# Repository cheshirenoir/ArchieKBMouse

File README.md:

# ArchieKBMouse
An adapter to allow Archimedes computers to use cheap PS/2 keyboards and mice. This is just a PCB/Schematic based on the hard work of the StarDot forum.
Based on a design by IanB, with some additional decoding by IanS

All I have done is put IanB's work into KiCAD, and designed a PCB off it, using some hinting from the schematic by IanS, so all credit and rights belong to them.
See: https://stardot.org.uk/forums/viewtopic.php?f=16&t=9334

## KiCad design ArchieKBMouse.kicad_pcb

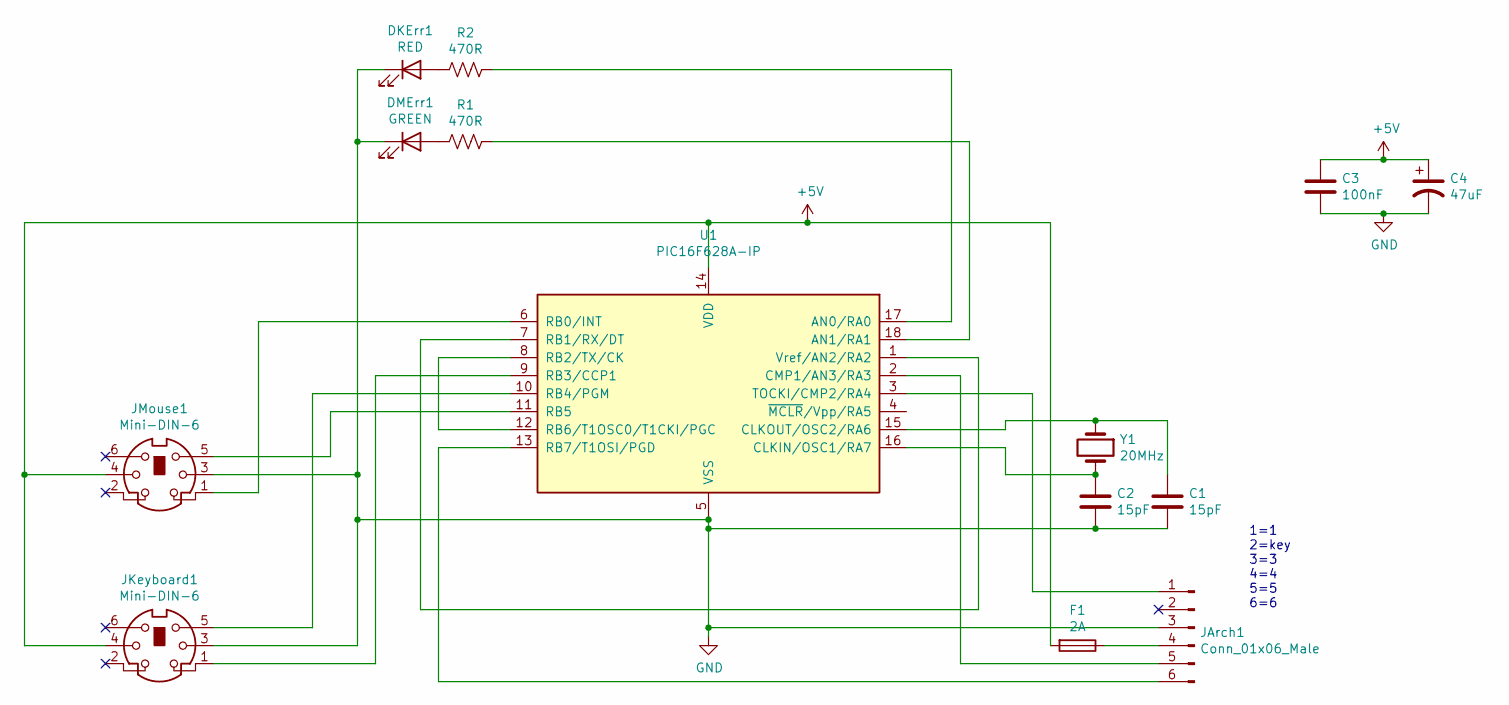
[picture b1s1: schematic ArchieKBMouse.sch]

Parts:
C1, C2: 15pF; C_Disc_D6.0mm_W2.5mm_P5.00mm
C3: 100nF; C_Disc_D6.0mm_W2.5mm_P5.00mm
C4: 47uF; CP_Radial_D5.0mm_P2.50mm
DKErr1: RED; LED_D5.0mm
DMErr1: GREEN; LED_D5.0mm
F1: 2A; Fuseholder_Cylinder-5x20mm_Schurter_FAB_0031-355x_Horizonta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
JArch1: Conn_01x06_Male; PinHeader_1x06_P2.54mm_Horizontal
JKeyboard1: Mini-DIN-6; Mini DIN 6 (PS2)
JMouse1: Mini-DIN-6; Mini DIN 6 (PS2)
R1, R2: 470R; R_Axial_DIN0207_L6.3mm_D2.5mm_P10.16mm_Horizontal
U1: PIC16F628A-IP; DIP-18_W7.62mm_Socket_LongPads
Y1: 20MHz; Crystal_HC49-U_Horizontal_1EP_style2

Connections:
+5V: C3.1, C4.1, F1.2, JKeyboard1.4, JMouse1.4, U1.14 (VDD)
GND: C1.2, C2.2, C3.2, C4.2, DKErr1.1 (K), DMErr1.1 (K), JArch1.3, JKeyboard1.3, JMouse1.3, U1.5 (VSS)
unnamed: C1.1, U1.15 (CLKOUT/OSC2/RA6), Y1.1
unnamed: C2.1, U1.16 (CLKIN/OSC1/RA7), Y1.2
unnamed: DKErr1.2 (A), R2.1
unnamed: DMErr1.2 (A), R1.1
unnamed: F1.1, JArch1.4
unnamed: JArch1.1, U1.3 (TOCKI/CMP2/RA4)
unnamed: JArch1.5, U1.2 (CMP1/AN3/RA3)
unnamed: JArch1.6, U1.13 (RB7/T1OSI/PGD)
unnamed: JKeyboard1.1, U1.9 (RB3/CCP1)
unnamed: JKeyboard1.5, U1.10 (RB4/PGM)
unnamed: JMouse1.1, U1.6 (RB0/INT)
unnamed: JMouse1.5, U1.11 (RB5)
unnamed: R1.2, U1.18 (AN1/RA1)
unnamed: R2.2, U1.17 (AN0/RA0)
unnamed: U1.1 (Vref/AN2/RA2), U1.7 (RB1/RX/DT)
unnamed: U1.8 (RB2/TX/CK), U1.12 (RB6/T1OSC0/T1CKI/PGC)

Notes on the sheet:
1=1 2=key 3=3 4=4 5=5 6=6

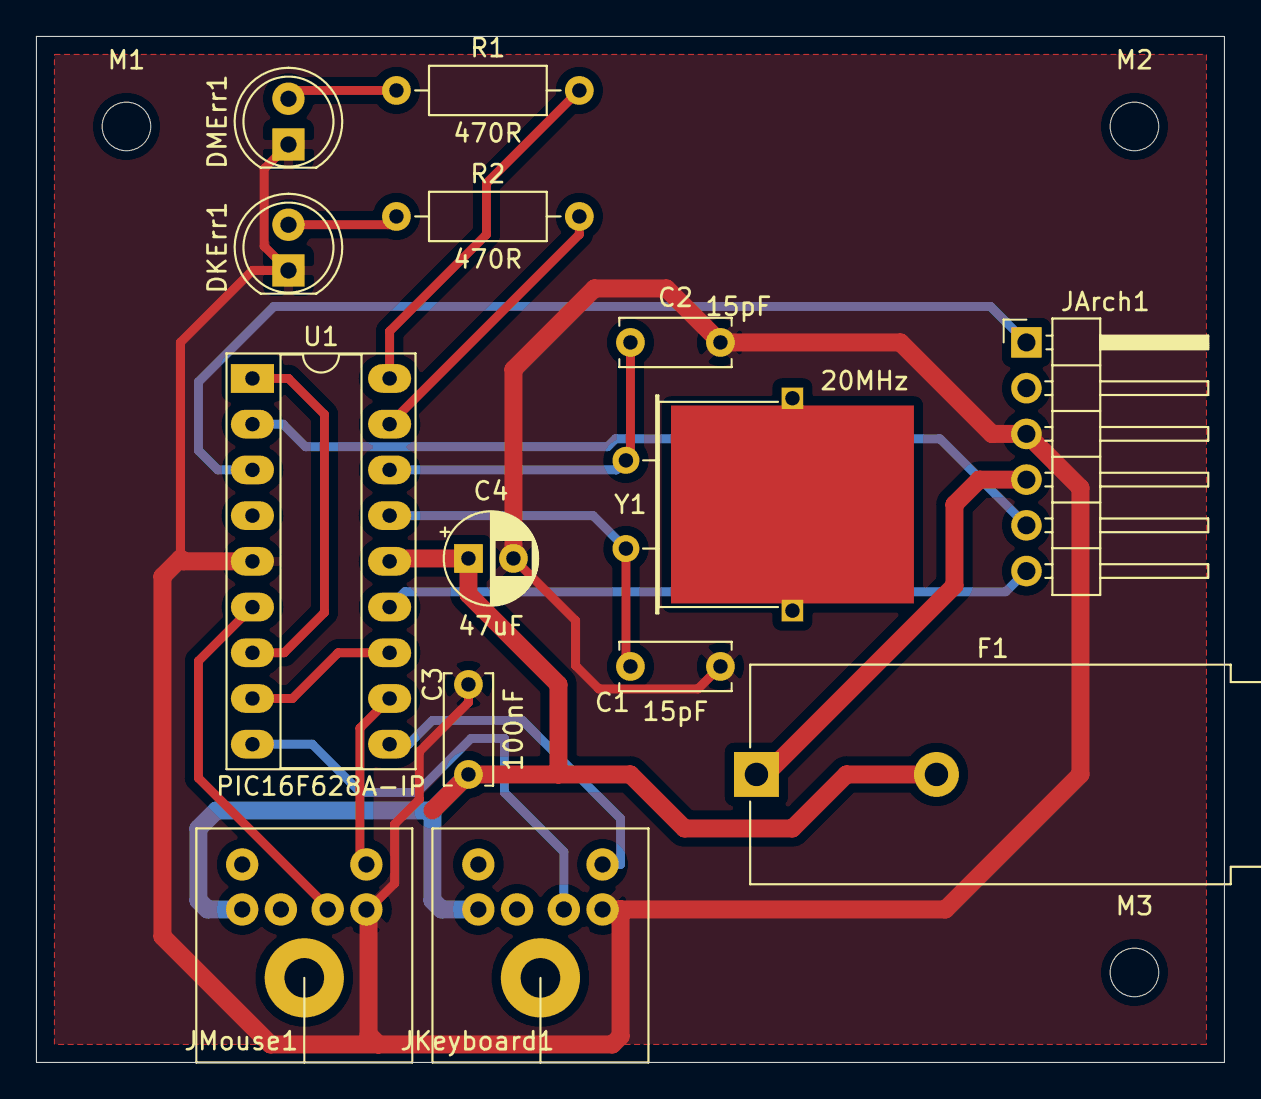
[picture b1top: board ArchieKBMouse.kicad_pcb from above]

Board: 2 copper layers, 66.0 x 57.0 mm, 17 parts (0 on the bottom side), 18 nets.

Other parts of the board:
M1, M2, M3: MountingHole_2.7mm_M2.5

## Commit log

2021-06-19 Add files via upload
    Initial cut of all KiCAD files

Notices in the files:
ArchieKBMouse.kicad_pcb:
CC BY SA
